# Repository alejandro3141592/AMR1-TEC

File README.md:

# AMR1-TEC
Vehículo eléctrico autónomo desarrollado por el Tecnológico de Monterrey para el transporte de materiales y personas dentro del Campus Puebla.

Este vehículo, es desarrollado por un grupo de profesor y alumnos del Tecnológico de Monterrey, es 100% eléctrico y cuenta con los sistemas principales de un vehículo: Frenos, Dirección, Tren Motriz, Arneses, Control. Actualmente, sigue en fase de desarrollo, es controlado via control remoto, pero se están hacinedo las adecuaciones pertinenetes para que sea autónmo, para el cual se incluirán tecnologías como el LIDAR, visión por computadora e inteligencia artidicial.

## Mi papel en el proyecto

Entre mis principales aportaciones a este proyecto, están el diseño de la [placa de potencia](https://github.com/alejandro3141592/AMR1-TEC/blob/main/PlacaDireccionV7.pdsprj) correspondiente a la dirección, también, contribuí al diseño de una placa que sería la encargada de la integración de varios sensores correspondientes a la navegación del vehículo, tanto en el [diagrama esquemático](https://github.com/alejandro3141592/AMR1-TEC/blob/main/NavegacionPlaca.sch) , como al [diseño de la PCB](https://github.com/alejandro3141592/AMR1-TEC/blob/main/NavegacionPlaca.brd).

De la misma manera, contribuí de forma importante a la documentación de todo el vehículo, y también  contribuí a la realización de algunos programas del vehículo, no obstante, por motivos de confidencialidad, no puedo compartirlos en este momento.

Finalmente, también soy tutor de otros estudiantes encargados de la instalación de arneses el vehículo autónomo AMR-TEC2, el cual pretnede ser la versión mejorada de éste primer vehículo.

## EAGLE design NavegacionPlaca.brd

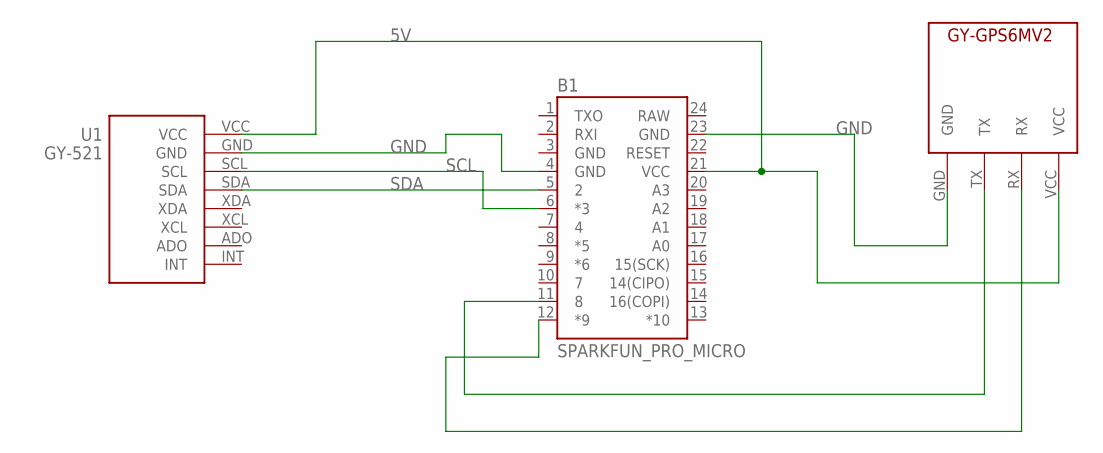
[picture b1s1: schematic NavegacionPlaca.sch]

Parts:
B1: SPARKFUN_PRO_MICRO
U1: GY-521
U$1: GY-GPS6MV2LIB; GY-GPS6M_FOOTPRINT

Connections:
5V: B1.21 (VCC), U1.VCC, U$1.VCC
GND: B1.3 (GND), B1.4 (GND), B1.23 (GND), U1.GND, U$1.GND
unnamed: B1.11 (8), U$1.TX
unnamed: B1.12 (*9), U$1.RX
RAW: B1.24 (RAW)
SCL: B1.6 (*3), U1.SCL
SDA: B1.5 (2), U1.SDA

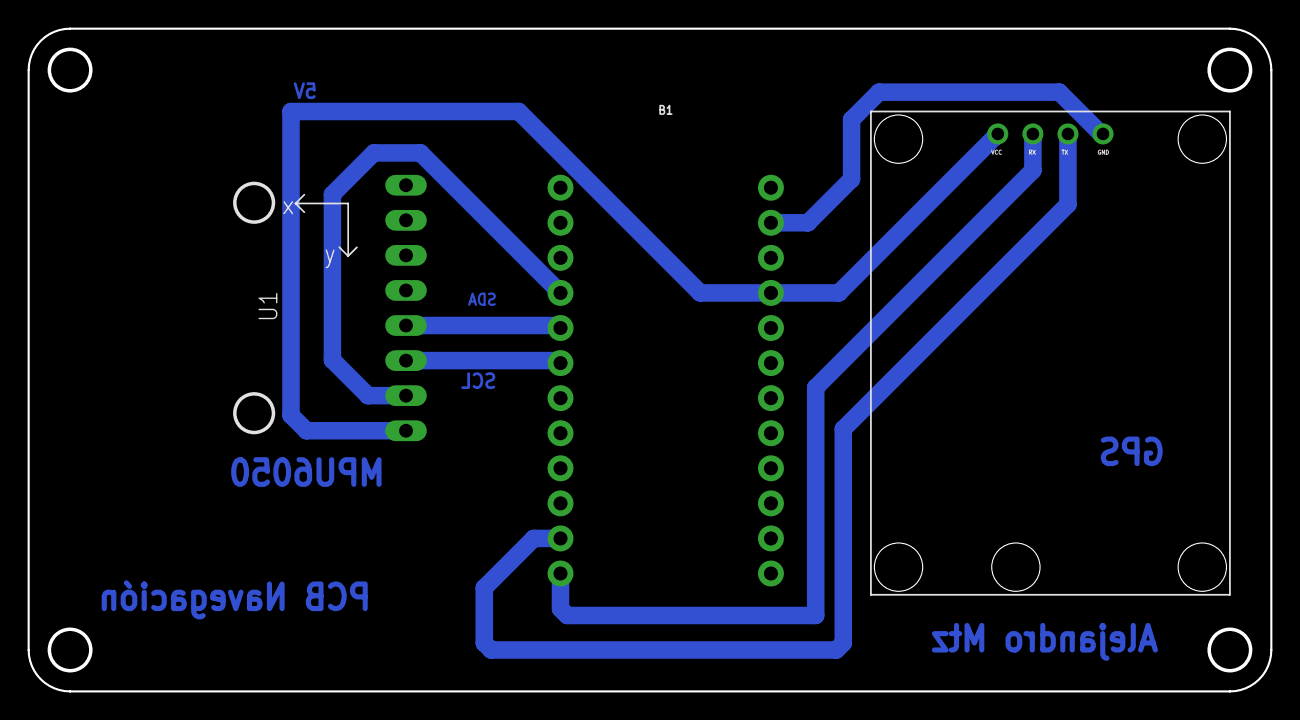
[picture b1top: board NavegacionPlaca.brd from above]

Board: 2 copper layers, 89.9 x 47.9 mm, 3 parts (0 on the bottom side), 6 nets.

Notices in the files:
parts and their libraries:
SparkFun-Boards: Licensing: Creative Commons ShareAlike 4.0 International - https://creativecommons.org/licenses/by-sa/4.0
